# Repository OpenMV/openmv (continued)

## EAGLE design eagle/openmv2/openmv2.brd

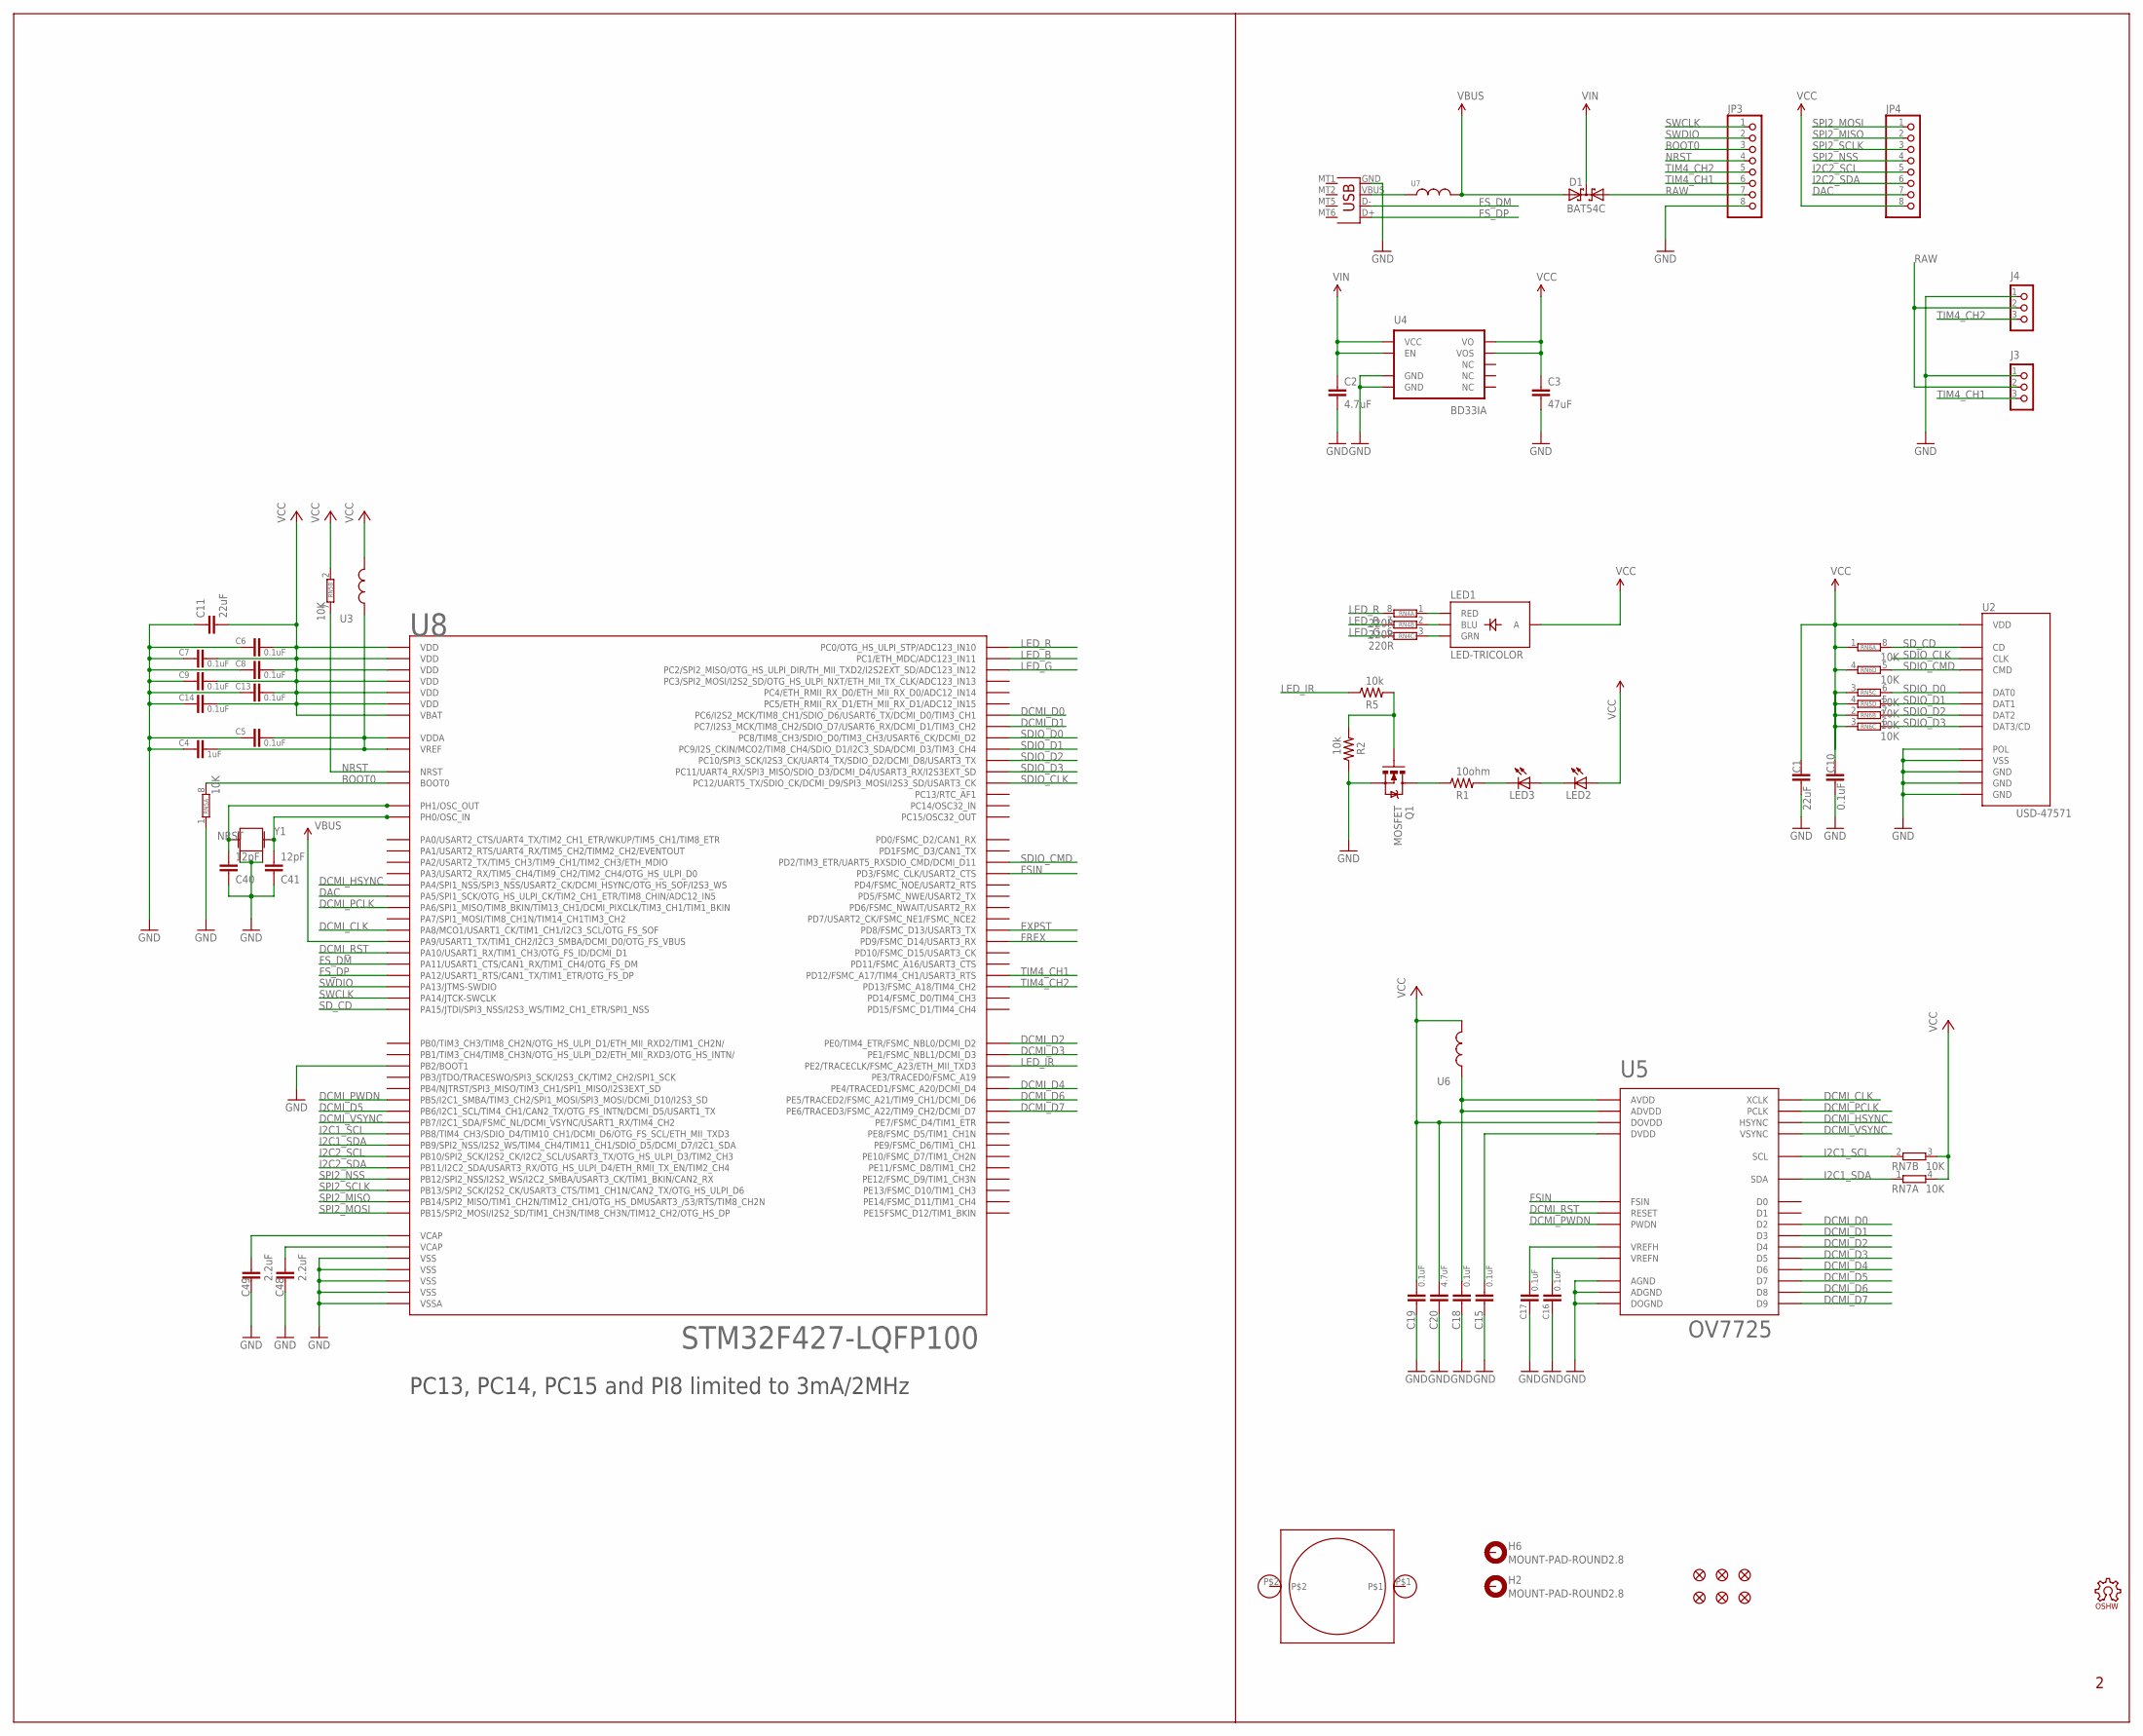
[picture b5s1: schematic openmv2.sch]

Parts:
C1, C11: 22uF; 0805
C2, C20: 4.7uF; 0603-CAP
C3: 47uF; 1206
C4: 1uF; 0603-CAP
C5, C6, C7, C8, C9, C10, C13, C14, C15, C16, C17, C18, C19: 0.1uF; 0603-CAP
C40, C41: 12pF; 0603-CAP
C48, C49: 2.2uF; 0603-CAP
D1: BAT54C; SOT23
H2, H6: MOUNT-PAD-ROUND2.8; 2,8-PAD
J3, J4: CON_HEADER_1X03; M1X3_SMD
JP1, JP2, JP5, JP6, JP7, JP8: FIDUCIAL1X2; FIDUCIAL-1X2
JP3, JP4: PINHD-1X8; 1X08
LED1: LED-TRICOLOR; LED-TRICOLOR-SMD
LED2, LED3: LED3MM
LOGO1: OSHW_LOGO_FILLX0150-NT; OSHW_FILLX150_NOTEXT
Q1: MOSFET; SOT23-3
R1: 10ohm; 0603-RES
R2, R5: 10k; 0603-RES
RN4: 220R; EXBV8V
RN5, RN6: 10K; EXBV8V
RN7: 10K; EXBV4V
U1: LENSMOUNT20MM; LENSMOUNT-20MM
U2: USD-47571
U3, U6, U7: INDUCTOR0603; 0603
U4: BD33IA; HTSOP-J8
U5: OV7725; CSP2-28
U8: STM32F427-LQFP100; LQFP100
X2: USB-MICROB
Y1: CRYSTAL2.5X2.0; CRYSTAL-2.5X2.0

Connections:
BOOT0: JP3.3, RN5.8 (2), U8.94 (BOOT0)
DAC: JP4.7, U8.30 (PA5/SPI1_SCK/OTG_HS_ULPI_CK/TIM2_CH1_ET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)
DCMI_CLK: U5.F3 (XCLK), U8.67 (PA8/MCO1/USART1_CK/TIM1_CH1/I2C3_SCL/OT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)
DCMI_D0: U5.F5 (D2), U8.63 (PC6/I2S2_MCK/TIM8_CH1/SDIO_D6/USART6_TX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)
DCMI_D1: U5.F2 (D3), U8.64 (PC7/I2S3_MCK/TIM8_CH2/SDIO_D7/USART6_RX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)
DCMI_D2: U5.D6 (D4), U8.97 (PE0/TIM4_ETR/FSMC_NBL0/DCMI_D2)
DCMI_D3: U5.D1 (D5), U8.98 (PE1/FSMC_NBL1/DCMI_D3)
DCMI_D4: U5.E6 (D6), U8.3 (PE4/TRACED1/FSMC_A20/DCMI_D4)
DCMI_D5: U5.E1 (D7), U8.92 (PB6/I2C1_SCL/TIM4_CH1/CAN2_TX/OTG_FS_IN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)
DCMI_D6: U5.F6 (D8), U8.4 (PE5/TRACED2/FSMC_A21/TIM9_CH1/DCMI_D6)
DCMI_D7: U5.F1 (D9), U8.5 (PE6/TRACED3/FSMC_A22/TIM9_CH2/DCMI_D7)
DCMI_HSYNC: U5.B6 (HSYNC), U8.29 (PA4/SPI1_NSS/SPI3_NSS/USART2_CK/DCMI_HS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)
DCMI_PCLK: U5.E4 (PCLK), U8.31 (PA6/SPI1_MISO/TIM8_BKIN/TIM13_CH1/DCMI_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)
DCMI_PWDN: U5.C1 (PWDN), U8.91 (PB5/I2C1_SMBA/TIM3_CH2/SPI1_MOSI/SPI3_M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)
DCMI_RST: U5.A2 (RESET), U8.69 (PA10/USART1_RX/TIM1_CH3/OTG_FS_ID/DCMI_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)
DCMI_VSYNC: U5.C6 (VSYNC), U8.93 (PB7/I2C1_SDA/FSMC_NL/DCMI_VSYNC/USART1_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)
EXPST: U8.55 (PD8/FSMC_D13/USART3_TX)
FREX: U8.56 (PD9/FSMC_D14/USART3_RX)
FSIN: U5.A4 (FSIN), U8.84 (PD3/FSMC_CLK/USART2_CTS)
FS_DM: U8.70 (PA11/USART1_CTS/CAN1_RX/TIM1_CH4/OTG_FS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), X2.D-
FS_DP: U8.71 (PA12/USART1_RTS/CAN1_TX/TIM1_ETR/OTG_FS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), X2.D+
GND: C1.2, C2.2, C3.2, C4.2, C5.2, C6.2, C7.2, C8.2, C9.2, C10.2, C11.1, C13.2, C14.2, C15.2, C16.2, C17.2, C18.2, C19.2, C20.2, C40.1, C41.1, C48.2, C49.2, J3.1, J4.1, JP3.8, Q1.2 (S), R2.1, RN5.1, U2.G$1 (GND), U2.G$2 (GND), U2.G$3 (GND), U2.G$4 (POL), U2.P$6 (VSS), U4.3 (GND), U4.P$1 (GND), U5.B1 (ADGND), U5.B4 (AGND), U5.F4 (DOGND), U8.10 (VSS), U8.20 (VSSA), U8.27 (VSS), U8.37 (PB2/BOOT1), U8.74 (VSS), U8.99 (VSS), X2.GND, Y1.2, Y1.4
I2C1_SCL: RN7.2 (1), U5.A5 (SCL), U8.95 (PB8/TIM4_CH3/SDIO_D4/TIM10_CH1/DCMI_D6/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)
I2C1_SDA: RN7.1, U5.B5 (SDA), U8.96 (PB9/SPI2_NSS/I2S2_WS/TIM4_CH4/TIM11_CH1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)
I2C2_SCL: JP4.5, U8.47 (PB10/SPI2_SCK/I2S2_CK/I2C2_SCL/USART3_T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)
I2C2_SDA: JP4.6, U8.48 (PB11/I2C2_SDA/USART3_RX/OTG_HS_ULPI_D4/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)
LED_B: RN4.7 (2), U8.16 (PC1/ETH_MDC/ADC123_IN11)
LED_G: RN4.6 (2), U8.17 (PC2/SPI2_MISO/OTG_HS_ULPI_DIR/TH_MII_TX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)
LED_IR: R5.1, U8.1 (PE2/TRACECLK/FSMC_A23/ETH_MII_TXD3)
LED_R: RN4.8 (2), U8.15 (PC0/OTG_HS_ULPI_STP/ADC123_IN10)
unnamed: C17.1, U5.A3 (VREFH)
unnamed: C40.2, U8.13 (PH1/OSC_OUT), Y1.3 (2)
unnamed: C16.1, U5.B2 (VREFN)
unnamed: C41.2, U8.12 (PH0/OSC_IN), Y1.1
unnamed: Q1.1 (G), R2.2, R5.2
unnamed: U7.1, X2.VBUS
unnamed: LED1.R (RED), RN4.1
unnamed: LED1.G (GRN), RN4.3 (1)
unnamed: LED3.K (C), R1.2
unnamed: LED1.B (BLU), RN4.2 (1)
unnamed: C4.1, C5.1, U3.1, U8.21 (VREF), U8.22 (VDDA)
unnamed: C18.1, U5.A1 (ADVDD), U5.B3 (AVDD), U6.1
unnamed: Q1.3 (D), R1.1
unnamed: C15.1, U5.E3 (DVDD)
unnamed: LED2.K (C), LED3.A
NRST: JP3.4, RN5.7 (2), U8.14 (NRST)
RAW: D1.1 (A1), J3.2, J4.2, JP3.7
SDIO_CLK: U2.P$5 (CLK), U8.80 (PC12/UART5_TX/SDIO_CK/DCMI_D9/SPI3_MOSI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)
SDIO_CMD: RN6.5 (2), U2.P$3 (CMD), U8.83 (PD2/TIM3_ETR/UART5_RXSDIO_CMD/DCMI_D11)
SDIO_D0: RN5.6 (2), U2.P$7 (DAT0), U8.65 (PC8/TIM8_CH3/SDIO_D0/TIM3_CH3/USART6_CK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)
SDIO_D1: RN5.5 (2), U2.P$8 (DAT1), U8.66 (PC9/I2S_CKIN/MCO2/TIM8_CH4/SDIO_D1/I2C3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)
SDIO_D2: RN6.7 (2), U2.P$1 (DAT2), U8.78 (PC10/SPI3_SCK/I2S3_CK/UART4_TX/SDIO_D2/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)
SDIO_D3: RN6.6 (2), U2.P$2 (DAT3/CD), U8.79 (PC11/UART4_RX/SPI3_MISO/SDIO_D3/DCMI_D4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)
SD_CD: RN6.8 (2), U2.G$5 (CD), U8.77 (PA15/JTDI/SPI3_NSS/I2S3_WS/TIM2_CH1_ETR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)
SPI2_MISO: JP4.2, U8.53 (PB14/SPI2_MISO/TIM1_CH2N/TIM12_CH1/OTG_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)
SPI2_MOSI: JP4.1, U8.54 (PB15/SPI2_MOSI/I2S2_SD/TIM1_CH3N/TIM8_C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)
SPI2_NSS: JP4.4, U8.51 (PB12/SPI2_NSS/I2S2_WS/I2C2_SMBA/USART3_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)
SPI2_SCLK: JP4.3, U8.52 (PB13/SPI2_SCK/I2S2_CK/USART3_CTS/TIM1_C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)
SWCLK: JP3.1, U8.76 (PA14/JTCK-SWCLK)
SWDIO: JP3.2, U8.72 (PA13/JTMS-SWDIO)
TIM4_CH1: J3.3, JP3.6, U8.59 (PD12/FSMC_A17/TIM4_CH1/USART3_RTS)
TIM4_CH2: J4.3, JP3.5, U8.60 (PD13/FSMC_A18/TIM4_CH2)
VBUS: D1.2 (A2), U7.2, U8.68 (PA9/USART1_TX/TIM1_CH2/I2C3_SMBA/DCMI_D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)
VCAP1: C49.1, U8.49 (VCAP)
VCAP2: C48.1, U8.73 (VCAP)
VCC: C1.1, C3.1, C6.1, C7.1, C8.1, C9.1, C10.1, C11.2, C13.1, C14.1, C19.1, C20.1, JP4.8, LED1.A, LED2.A, RN5.2 (1), RN5.3 (1), RN5.4 (1), RN6.1, RN6.2 (1), RN6.3 (1), RN6.4 (1), RN7.3 (2), RN7.4 (2), U2.P$4 (VDD), U3.2, U4.1 (VO), U4.2 (VOS), U5.E5 (DOVDD), U6.2, U8.6 (VBAT), U8.11 (VDD), U8.19 (VDD), U8.28 (VDD), U8.50 (VDD), U8.75 (VDD), U8.100 (VDD)
VIN: C2.1, D1.3 (CC), U4.5 (EN), U4.8 (VCC)

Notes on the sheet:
PC13, PC14, PC15 and PI8 limited to 3mA/2MHz

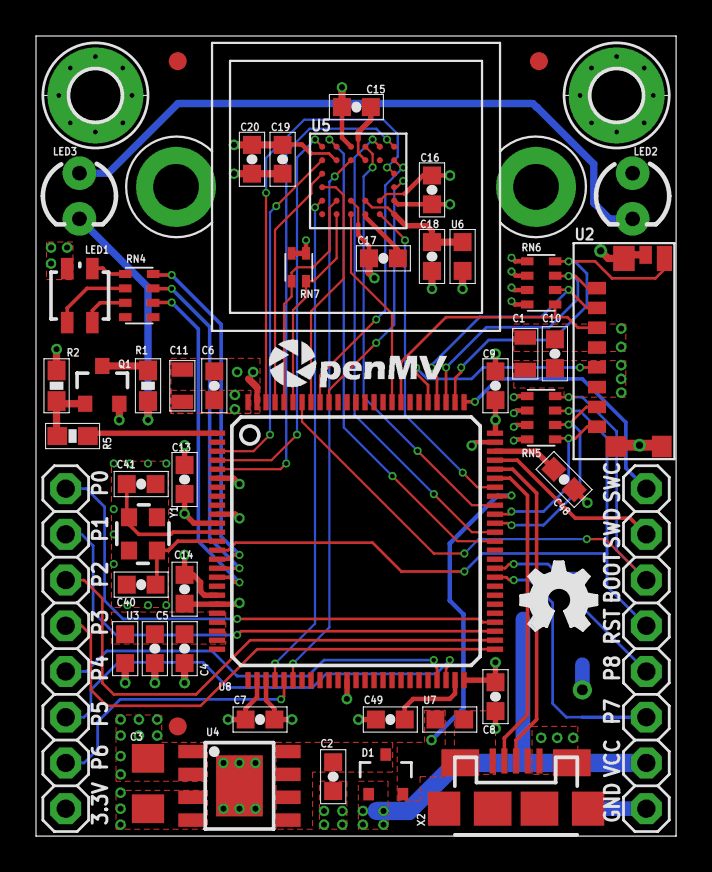
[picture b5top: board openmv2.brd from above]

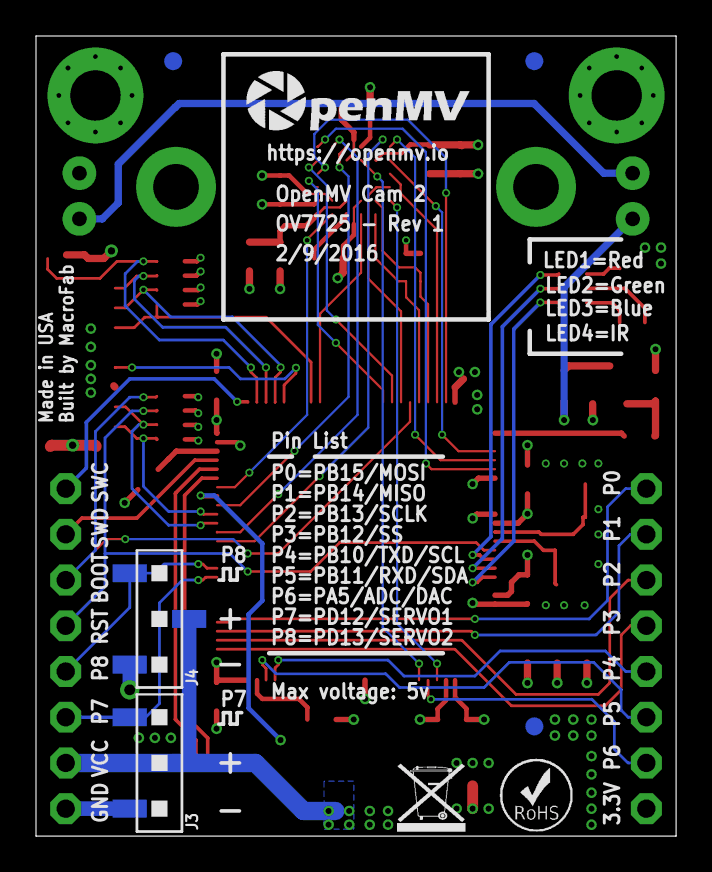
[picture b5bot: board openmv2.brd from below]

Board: 4 copper layers, 35.6 x 44.5 mm, 62 parts (8 on the bottom side), 65 nets.

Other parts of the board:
U$1: WEEE
U$2: ROHS
U$3: OMV-LOGO
U$4: OMV-LOGO-SMALL

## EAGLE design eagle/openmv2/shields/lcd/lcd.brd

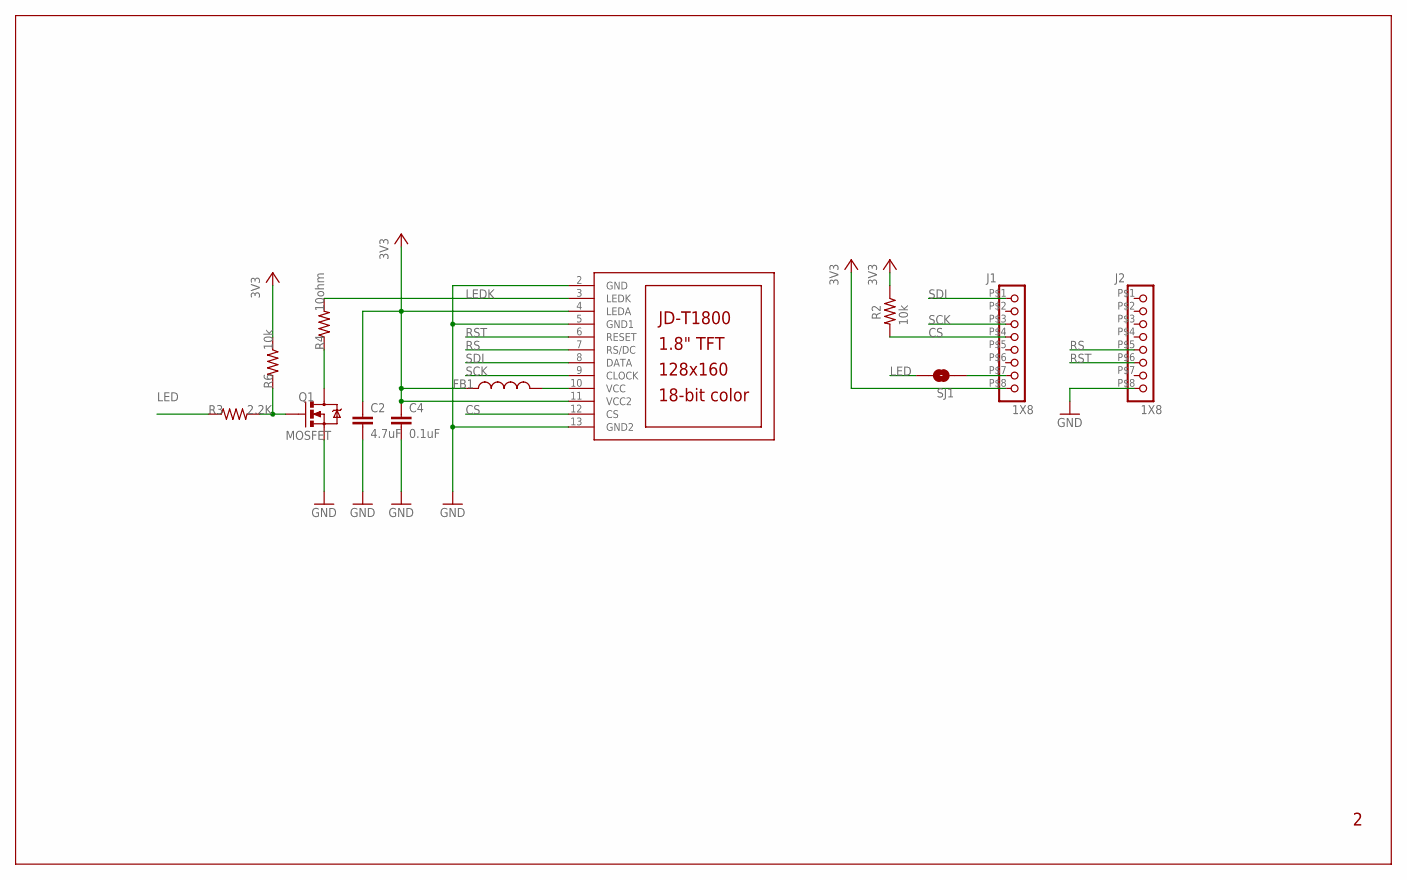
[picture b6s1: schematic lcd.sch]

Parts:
C2: 4.7uF; 0603-CAP
C4: 0.1uF; 0603-CAP
FB1: INDUCTOR0603; 0603
J1, J2: 1X8
LCD1: JD-T1800
Q1: MOSFET; SOT23-3
R2, R6: 10k; 0603-RES
R3: 2.2K; 0603-RES
R4: 10ohm; 0603-RES
SJ1: SOLDERJUMPERTRACE; SJ_2S-TRACE

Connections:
3V3: C2.1, C4.1, FB1.1, J1.P$8 (8), LCD1.4 (LEDA), LCD1.11 (VCC2), R2.1, R6.1
CS: J1.P$4 (4), LCD1.12 (CS), R2.2
GND: C2.2, C4.2, J2.P$8 (8), LCD1.2 (GND), LCD1.5 (GND1), LCD1.13 (GND2), Q1.2 (S)
LED: R3.1, SJ1.2
LEDK: LCD1.3 (LEDK), R4.2
unnamed: J1.P$7 (7), SJ1.1
unnamed: Q1.1 (G), R3.2, R6.2
unnamed: Q1.3 (D), R4.1
RS: J2.P$5 (5), LCD1.7 (RS/DC)
RST: J2.P$6 (6), LCD1.6 (RESET)
SCK: J1.P$3 (3), LCD1.9 (CLOCK)
SDI: J1.P$1 (1), LCD1.8 (DATA)
VDDA: FB1.2, LCD1.10 (VCC)

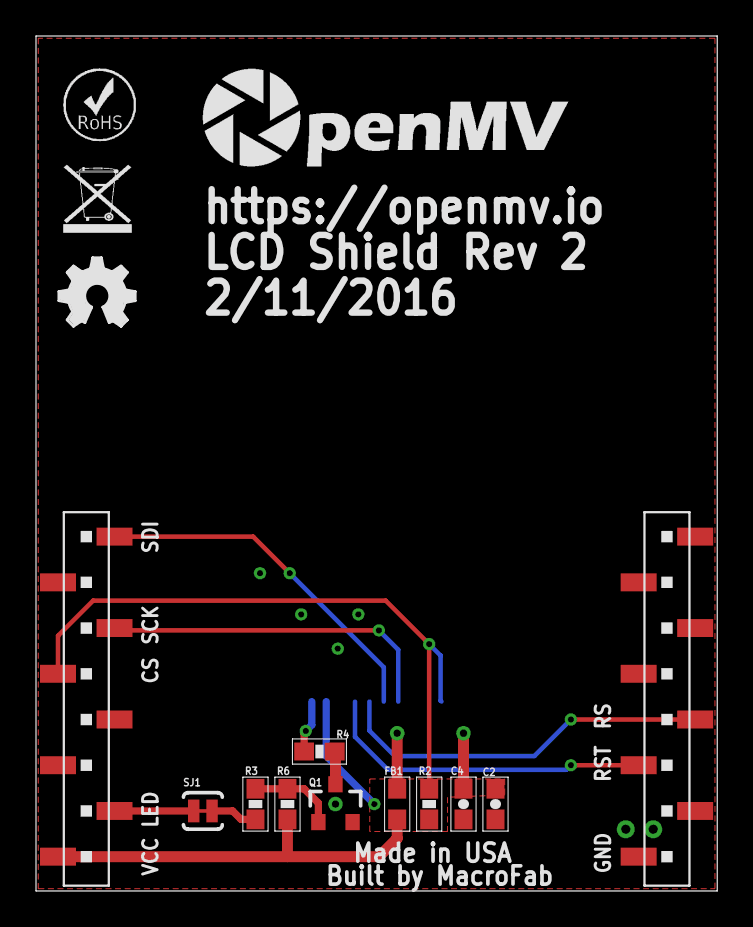
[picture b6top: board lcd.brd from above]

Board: 2 copper layers, 37.8 x 47.5 mm, 16 parts (1 on the bottom side), 13 nets.

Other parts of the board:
U$2: ROHS
U$3: WEEE
U$4: OMV-LOGO-BIG
U$5: OSHW_FILLX150_NOTEXT

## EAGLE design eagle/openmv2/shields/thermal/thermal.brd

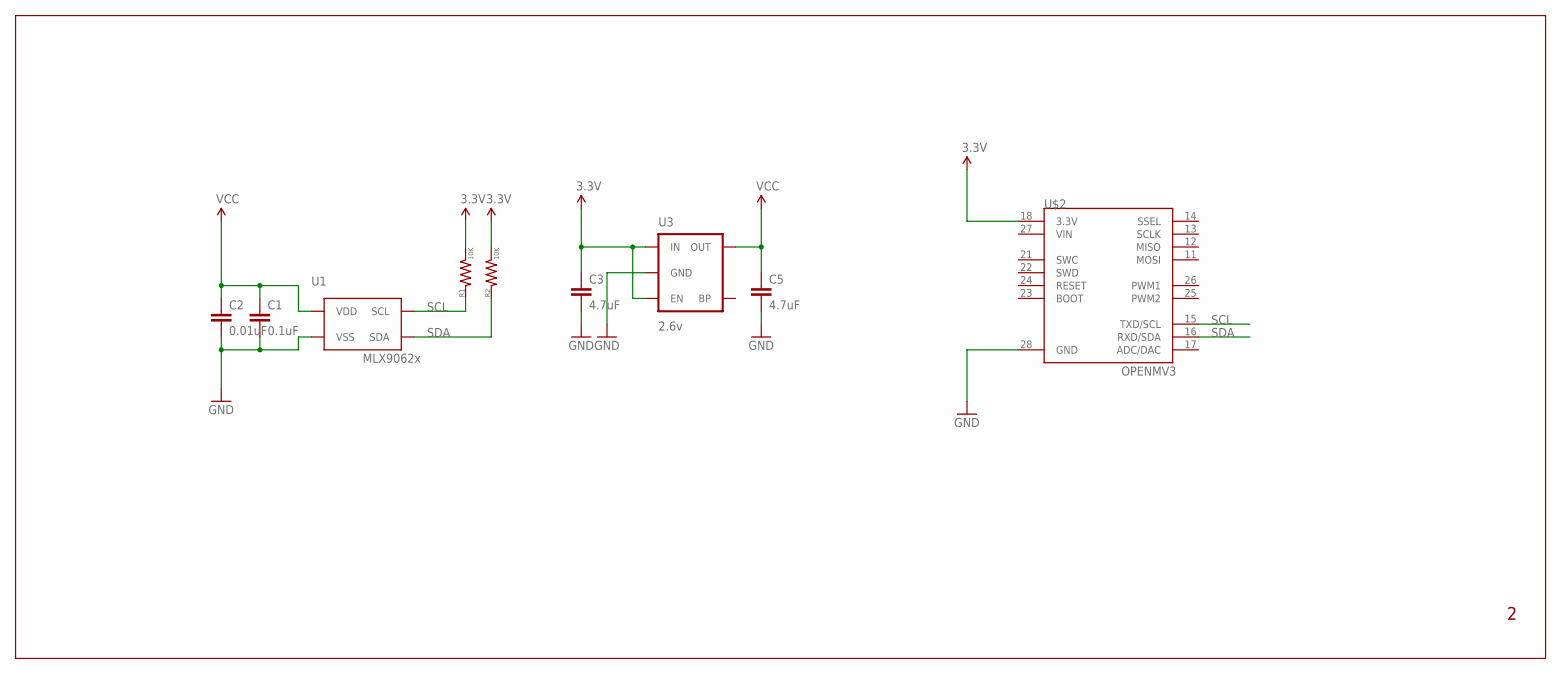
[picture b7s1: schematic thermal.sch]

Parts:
C1: 0.1uF; 0603-CAP
C2: 0.01uF; 0603-CAP
C3, C5: 4.7uF; 0603-CAP
R1, R2: 10K; 0603-RES
U1: MLX9062x; TO39/4
U3: 2.6v; SOT23-5
U$2: OPENMV3

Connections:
3.3V: C3.1, R1.1, R2.1, U3.1 (IN), U3.3 (EN), U$2.18 (3.3V)
GND: C1.2, C2.2, C3.2, C5.2, U1.4 (VSS), U3.2 (GND), U$2.28 (GND)
SCL: R1.2, U1.1 (SCL), U$2.15 (TXD/SCL)
SDA: R2.2, U1.2 (SDA), U$2.16 (RXD/SDA)
VCC: C1.1, C2.1, C5.1, U1.3 (VDD), U3.5 (OUT)
VIN: U$2.27 (VIN)

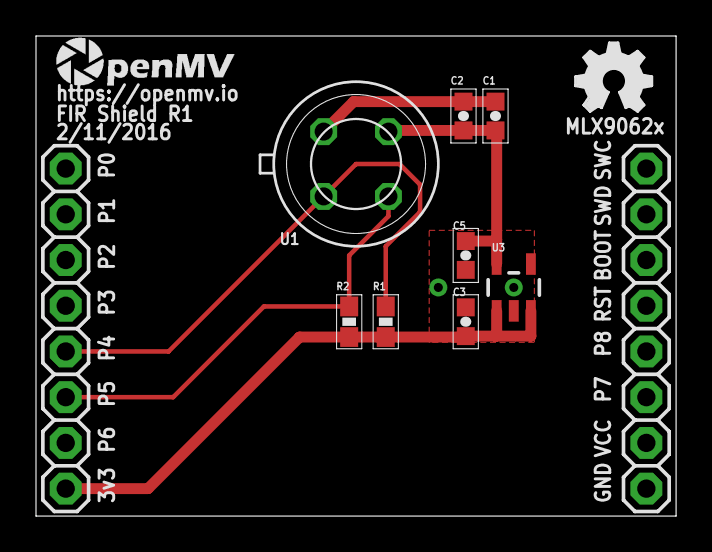
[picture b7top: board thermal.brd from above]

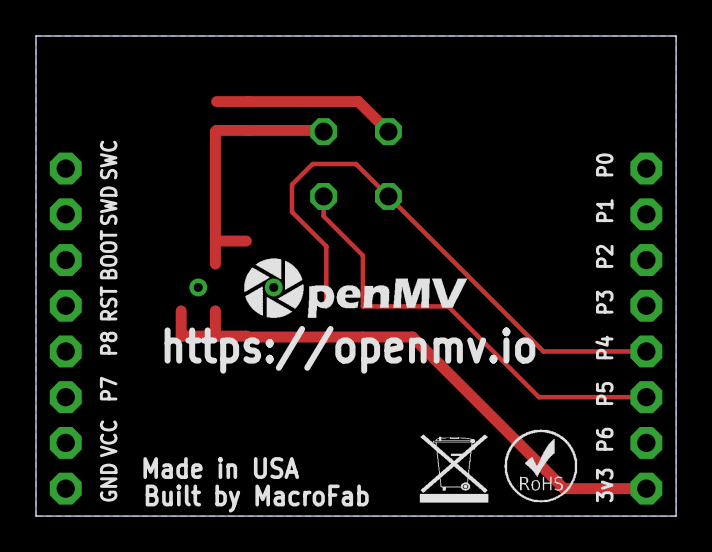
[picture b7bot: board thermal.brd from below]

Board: 2 copper layers, 35.6 x 26.7 mm, 14 parts (3 on the bottom side), 5 nets.

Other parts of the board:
U$3: OMV-LOGO
U$5: ROHS
U$6: WEEE
U$7: OSHW_FILLX150_NOTEXT
U$10: OMV-LOGO-SMALL

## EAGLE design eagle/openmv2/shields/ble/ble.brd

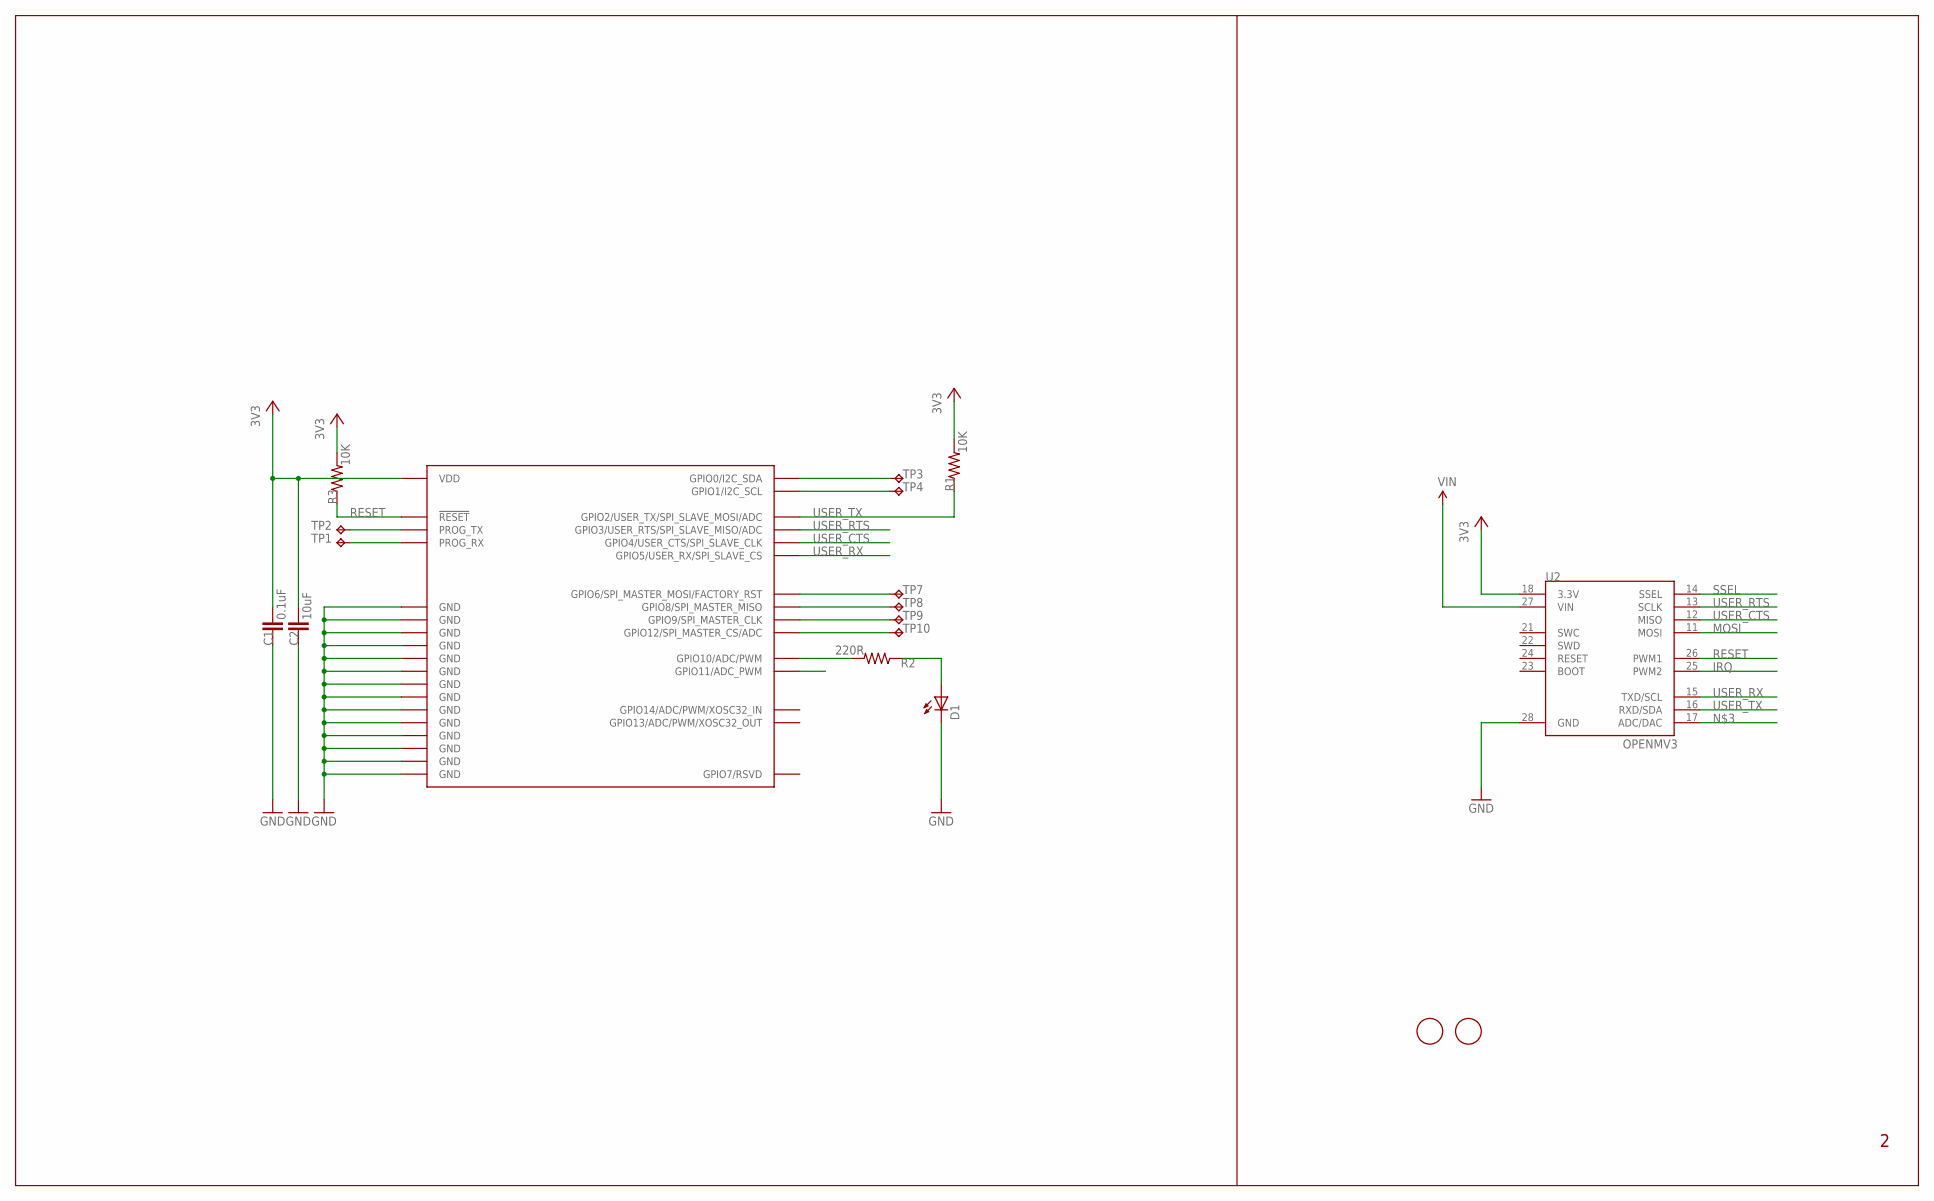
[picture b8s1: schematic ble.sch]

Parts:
C1: 0.1uF; 0603-CAP
C2: 10uF; 0805
D1: LED0603; LED-0603
R1, R3: 10K; 0603-RES
R2: 220R; 0603-RES
TP1, TP2, TP3, TP4, TP7, TP8, TP9, TP10: TPTP12R; TP12R
U2: OPENMV3
U$1, U$2: FIDUCIAL; FIDUCIAL_1MM
U$3: AMS00X

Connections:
3V3: C1.2, C2.2, R1.2, R3.2, U2.18 (3.3V), U$3.P$21 (VDD)
GND: C1.1, C2.1, D1.C, U2.28 (GND), U$3.P$1 (GND), U$3.P$19 (GND), U$3.P$22 (GND), U$3.P$23 (GND), U$3.P$24 (GND), U$3.P$25 (GND), U$3.P$26 (GND), U$3.P$27 (GND), U$3.P$28 (GND), U$3.P$29 (GND), U$3.P$30 (GND), U$3.P$31 (GND), U$3.P$32 (GND), U$3.P$33 (GND)
IRQ: U2.25 (PWM2)
MOSI: U2.11 (MOSI)
unnamed: TP7.TP, U$3.P$11 (GPIO6/SPI_MASTER_MOSI/FACTORY_RST)
unnamed: TP3.TP, U$3.P$4 (GPIO0/I2C_SDA)
unnamed: TP4.TP, U$3.P$5 (GPIO1/I2C_SCL)
unnamed: TP2.TP, U$3.P$3 (PROG_TX)
unnamed: TP1.TP, U$3.P$2 (PROG_RX)
unnamed: TP8.TP, U$3.P$13 (GPIO8/SPI_MASTER_MISO)
unnamed: TP9.TP, U$3.P$14 (GPIO9/SPI_MASTER_CLK)
unnamed: TP10.TP, U$3.P$17 (GPIO12/SPI_MASTER_CS/ADC)
unnamed: D1.A, R2.1
unnamed: R2.2, U$3.P$15 (GPIO10/ADC/PWM)
RESET: R3.1, U2.26 (PWM1), U$3.P$8 (!RESET)
SSEL: U2.14 (SSEL)
USER_CTS: U2.12 (MISO), U$3.P$9 (GPIO4/USER_CTS/SPI_SLAVE_CLK)
USER_RTS: U2.13 (SCLK), U$3.P$7 (GPIO3/USER_RTS/SPI_SLAVE_MISO/ADC)
USER_RX: U2.15 (TXD/SCL), U$3.P$10 (GPIO5/USER_RX/SPI_SLAVE_CS)
USER_TX: R1.1, U2.16 (RXD/SDA), U$3.P$6 (GPIO2/USER_TX/SPI_SLAVE_MOSI/ADC)
VIN: U2.27 (VIN)

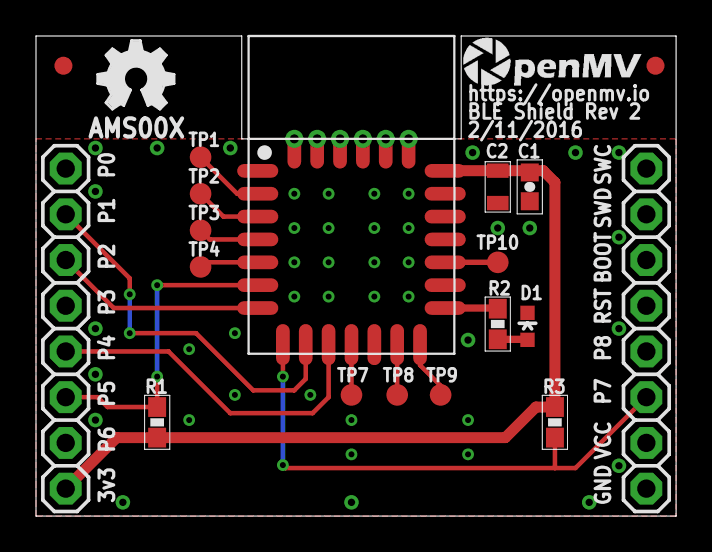
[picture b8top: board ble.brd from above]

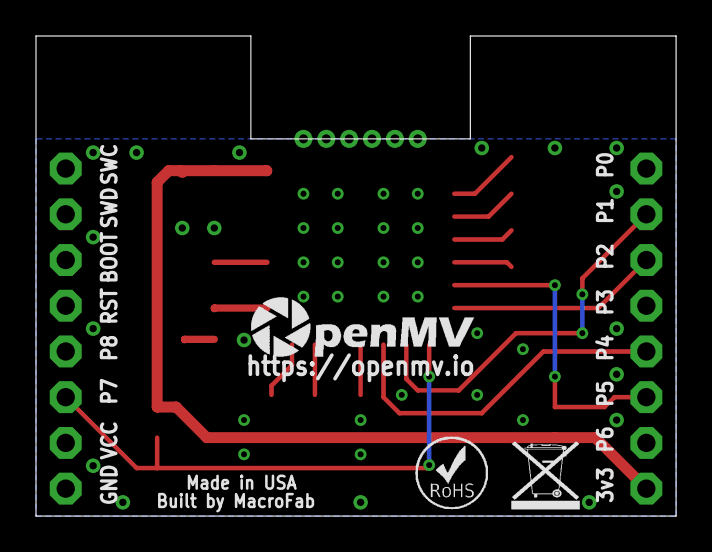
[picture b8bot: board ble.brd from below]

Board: 2 copper layers, 35.6 x 26.7 mm, 23 parts (3 on the bottom side), 17 nets.

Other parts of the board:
U$4: OMV-LOGO
U$5: OSHW_FILLX150_NOTEXT
U$7: OMV-LOGO-SMALL
U$8: WEEE
U$9: ROHS

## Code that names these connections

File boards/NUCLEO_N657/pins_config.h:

// NUCLEO-N657X0-Q pin definitions (see board_config.h).

// SPI5: Arduino D10 (NSS), D11 (MOSI), D12 (MISO), D13 (SCK)
OMV_GPIO_DEFINE(E, 15, AF5, SPI5)       // SPI5_SCK
OMV_GPIO_DEFINE(G, 1,  AF5, SPI5)       // SPI5_MISO
OMV_GPIO_DEFINE(G, 2,  AF5, SPI5)       // SPI5_MOSI
OMV_GPIO_DEFINE(A, 3,  AF5, SPI5)       // SPI5_NSS

// I2C1: Arduino D15 (SCL), D14 (SDA)
OMV_GPIO_DEFINE(H, 9,  AF4, I2C1)       // I2C1_SCL
OMV_GPIO_DEFINE(C, 1,  AF4, I2C1)       // I2C1_SDA

// I2C2: camera connector
OMV_GPIO_DEFINE(B, 10, AF4, I2C2)       // I2C2_SCL
OMV_GPIO_DEFINE(B, 11, AF4, I2C2)       // I2C2_SDA

// I2C4
OMV_GPIO_DEFINE(E, 13, AF4, I2C4)       // I2C4_SCL
OMV_GPIO_DEFINE(E, 14, AF4, I2C4)       // I2C4_SDA

// Camera connector control lines
OMV_GPIO_DEFINE(O, 5,  NONE, GPIO)      // CSI_RESET (NRST_CAM, active low, VDDIO2 3.3V)
OMV_GPIO_DEFINE(A, 0,  NONE, GPIO)      // CSI_POWER (EN_CAM, high = on)
